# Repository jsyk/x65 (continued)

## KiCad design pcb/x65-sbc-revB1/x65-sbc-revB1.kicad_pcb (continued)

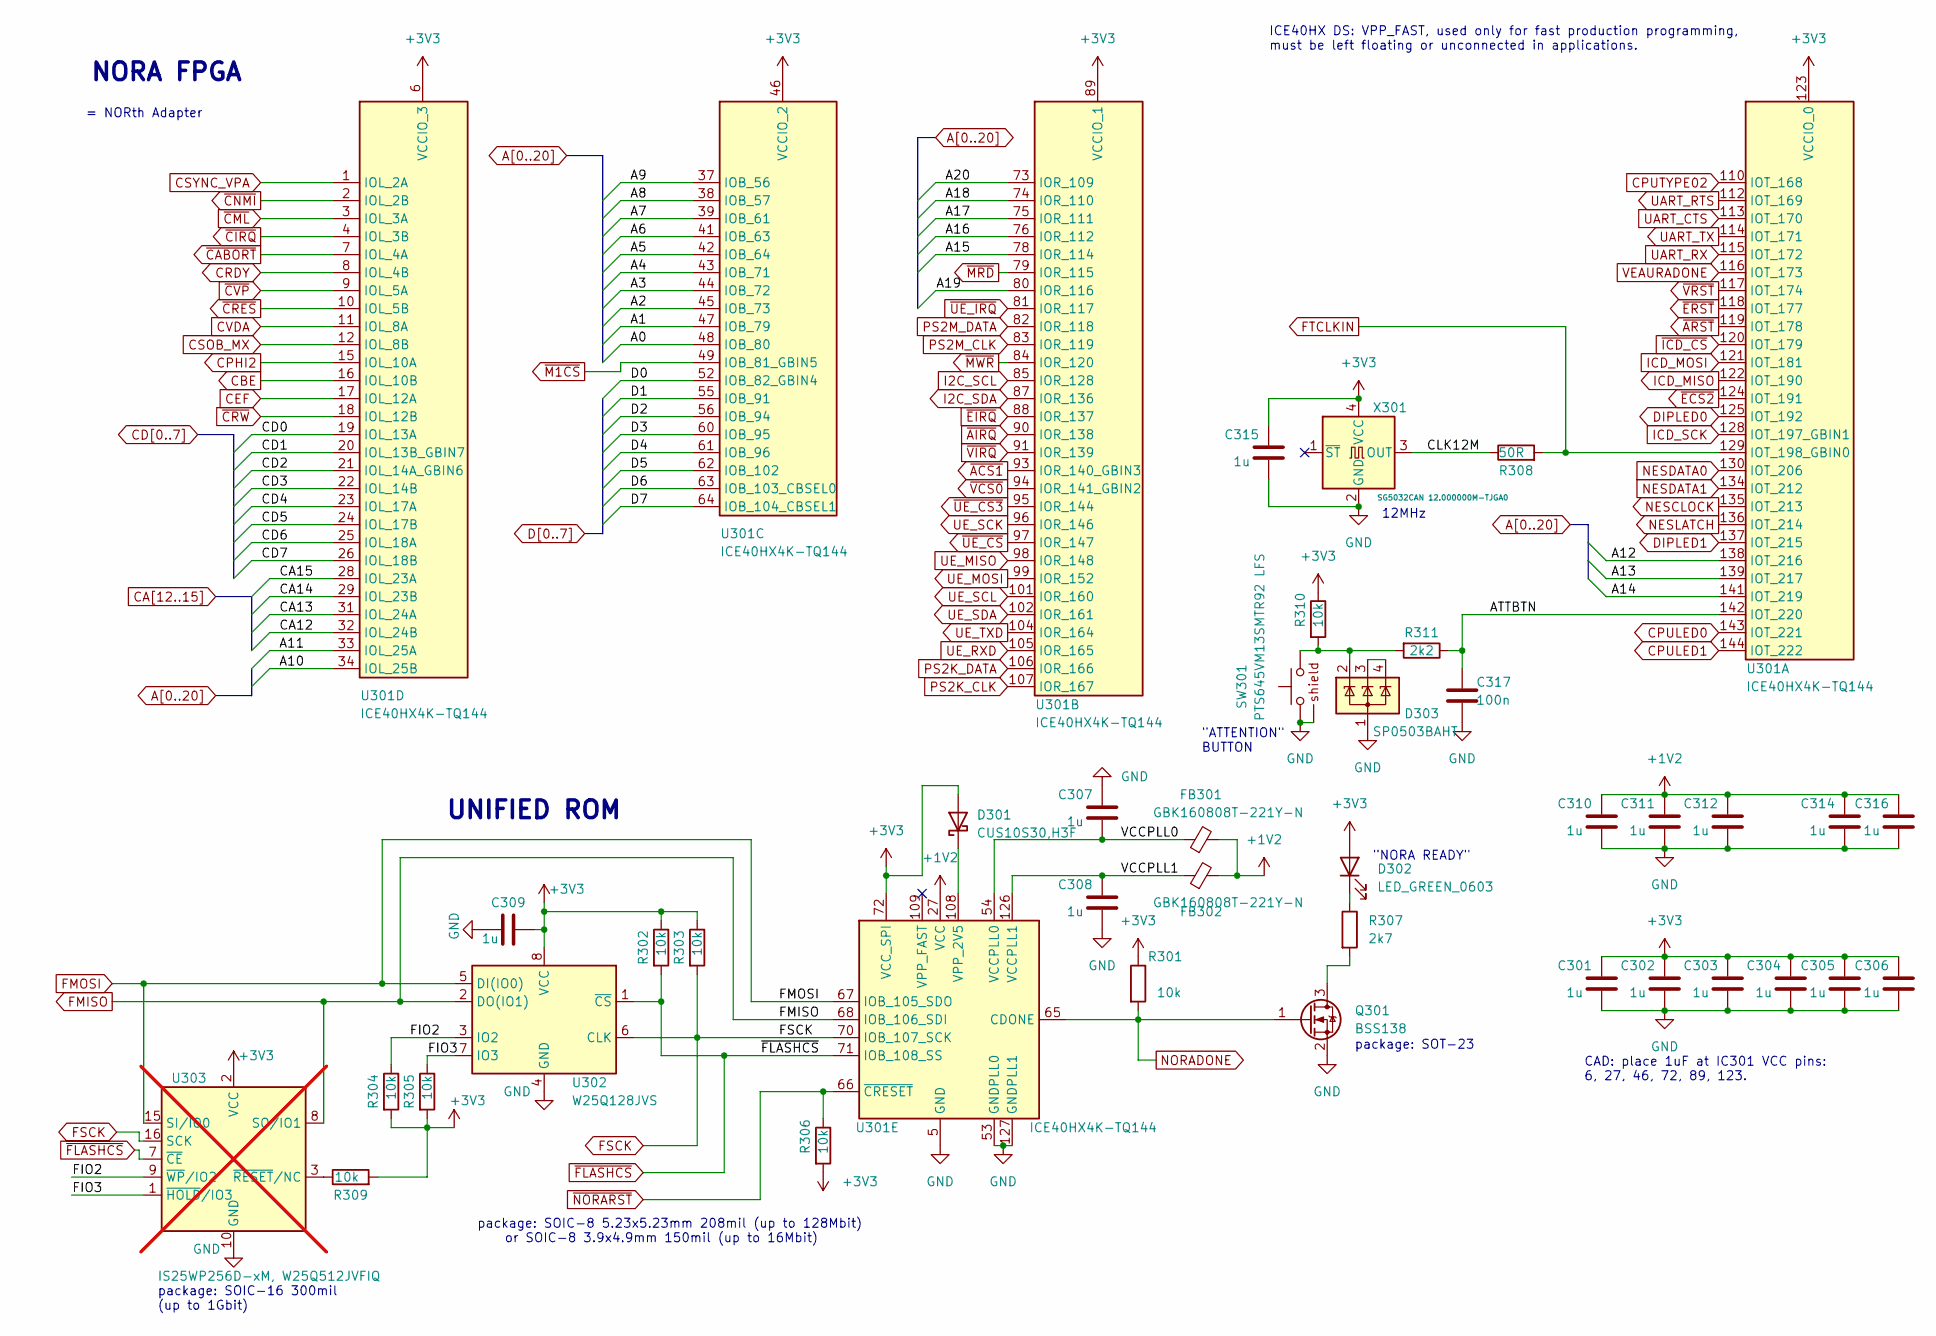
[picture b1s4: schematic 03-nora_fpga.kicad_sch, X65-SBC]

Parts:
C301, C302, C303, C304, C305, C306, C307, C308, C309, C310, C311, C312, C314, C315, C316: 1u; C_0603_1608Metric_Pad1.08x0.95mm_HandSolder
C317: 100n; C_0603_1608Metric_Pad1.08x0.95mm_HandSolder
D301: CUS10S30,H3F; D_SOD-323_HandSoldering
D302: LED_GREEN_0603; LED_0603_1608Metric_Pad1.05x0.95mm_HandSolder
D303: SP0503BAHT; SOT-143
FB301, FB302: GBK160808T-221Y-N; R_0603_1608Metric_Pad0.98x0.95mm_HandSolder
Q301: BSS138; SOT-23
R301, R302, R303, R304, R305, R306, R309, R310: 10k; R_0603_1608Metric_Pad0.98x0.95mm_HandSolder
R307: 2k7; R_0603_1608Metric_Pad0.98x0.95mm_HandSolder
R308: 50R; R_0603_1608Metric_Pad0.98x0.95mm_HandSolder
R311: 2k2; R_0603_1608Metric_Pad0.98x0.95mm_HandSolder
SW301: PTS645VM13SMTR92 LFS
U301: ICE40HX4K-TQ144; TQFP-144_20x20mm_P0.5mm
U302: W25Q128JVS; SOIC-8_5.23x5.23mm_P1.27mm_Extended
U303: IS25WP256D-xM, W25Q512JVFIQ; SOIC-16W_7.5x10.3mm_P1.27mm; not fitted
X301: SG5032CAN 12.000000M-TJGA0; Oscillator_SMD_SeikoEpson_SG8002LB-4Pin_5.0x3.2mm_HandSolde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

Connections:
+1V2: C310.1, C311.1, C312.1, C314.1, C316.1, FB301.2, FB302.2, U301.27 (VCC), U301.40 (VCC), U301.92 (VCC), U301.111 (VCC); also elsewhere on the board
+3V3: C301.1, C302.1, C303.1, C304.1, C305.1, C306.1, C309.1, C315.1, D301.2 (A), D302.2 (A), R301.1, R302.1, R303.1, R304.2, R305.2, R306.2, R309.2, R310.1, U301.6 (VCCIO_3), U301.30 (VCCIO_3), U301.46 (VCCIO_2), U301.57 (VCCIO_2), U301.72 (VCC_SPI), U301.89 (VCCIO_1), U301.100 (VCCIO_1), U301.123 (VCCIO_0), U301.131 (VCCIO_0), U302.8 (VCC), U303.2 (VCC), X301.4 (VCC); also elsewhere on the board
/NORA FPGA/ATTBTN: C317.1, R311.1, U301.142 (IOT_220)
/NORA FPGA/CLK12M: R308.1, X301.3 (OUT)
/NORA FPGA/FIO2: R304.1, U302.3 (IO2), U303.9 (~WP/IO2)
/NORA FPGA/FIO3: R305.1, U302.7 (IO3), U303.1 (~HOLD/IO3)
/NORA FPGA/VCCPLL0: C307.2, FB301.1, U301.54 (VCCPLL0)
/NORA FPGA/VCCPLL1: C308.1, FB302.1, U301.126 (VCCPLL1)
A0: U301.48 (IOB_80); also elsewhere on the board
A1: U301.47 (IOB_79); also elsewhere on the board
A2: U301.45 (IOB_73); also elsewhere on the board
A3: U301.44 (IOB_72); also elsewhere on the board
A4: U301.43 (IOB_71); also elsewhere on the board
A5: U301.42 (IOB_64); also elsewhere on the board
A6: U301.41 (IOB_63); also elsewhere on the board
A7: U301.39 (IOB_61); also elsewhere on the board
A8: U301.38 (IOB_57); also elsewhere on the board
A9: U301.37 (IOB_56); also elsewhere on the board
A10: U301.34 (IOL_25B); also elsewhere on the board
A11: U301.33 (IOL_25A); also elsewhere on the board
A12: U301.138 (IOT_216); also elsewhere on the board
A13: U301.139 (IOT_217); also elsewhere on the board
A14: U301.141 (IOT_219); also elsewhere on the board
A15: U301.78 (IOR_114); also elsewhere on the board
A16: U301.76 (IOR_112); also elsewhere on the board
A17: U301.75 (IOR_111); also elsewhere on the board
A18: U301.74 (IOR_110); also elsewhere on the board
A19: U301.80 (IOR_116); also elsewhere on the board
A20: U301.73 (IOR_109); also elsewhere on the board
CA12: U301.32 (IOL_24B); also elsewhere on the board
CA13: U301.31 (IOL_24A); also elsewhere on the board
CA14: U301.29 (IOL_23B); also elsewhere on the board
CA15: U301.28 (IOL_23A); also elsewhere on the board
CBE: U301.16 (IOL_10B); also elsewhere on the board
CD0: U301.19 (IOL_13A); also elsewhere on the board
CD1: U301.20 (IOL_13B_GBIN7); also elsewhere on the board
CD2: U301.21 (IOL_14A_GBIN6); also elsewhere on the board
CD3: U301.22 (IOL_14B); also elsewhere on the board
CD4: U301.23 (IOL_17A); also elsewhere on the board
CD5: U301.24 (IOL_17B); also elsewhere on the board
CD6: U301.25 (IOL_18A); also elsewhere on the board
CD7: U301.26 (IOL_18B); also elsewhere on the board
CEF: U301.17 (IOL_12A); also elsewhere on the board
CPHI2: U301.15 (IOL_10A); also elsewhere on the board
CPULED0: U301.143 (IOT_221); also elsewhere on the board
CPULED1: U301.144 (IOT_222); also elsewhere on the board
CPUTYPE02: U301.110 (IOT_168); also elsewhere on the board
CRDY: U301.8 (IOL_4B); also elsewhere on the board
CSOB_MX: U301.12 (IOL_8B); also elsewhere on the board
CSYNC_VPA: U301.1 (IOL_2A); also elsewhere on the board
CVDA: U301.11 (IOL_8A); also elsewhere on the board
D0: U301.52 (IOB_82_GBIN4); also elsewhere on the board
D1: U301.55 (IOB_91); also elsewhere on the board
D2: U301.56 (IOB_94); also elsewhere on the board
D3: U301.60 (IOB_95); also elsewhere on the board
D4: U301.61 (IOB_96); also elsewhere on the board
D5: U301.62 (IOB_102); also elsewhere on the board
D6: U301.63 (IOB_103_CBSEL0); also elsewhere on the board
D7: U301.64 (IOB_104_CBSEL1); also elsewhere on the board
DIPLED0: U301.125 (IOT_192); also elsewhere on the board
DIPLED1: U301.137 (IOT_215); also elsewhere on the board
FMISO: U301.68 (IOB_106_SDI), U302.2 (DO(IO1)), U303.8 (SO/IO1); also elsewhere on the board
FMOSI: U301.67 (IOB_105_SDO), U302.5 (DI(IO0)), U303.15 (SI/IO0); also elsewhere on the board
FSCK: R303.2, U301.70 (IOB_107_SCK), U302.6 (CLK), U303.16 (SCK); also elsewhere on the board
FTCLKIN: R308.2, U301.129 (IOT_198_GBIN0); also elsewhere on the board
GND: C301.2, C302.2, C303.2, C304.2, C305.2, C306.2, C307.1, C308.2, C309.2, C310.2, C311.2, C312.2, C314.2, C315.2, C316.2, C317.2, D303.1 (A), Q301.2 (S), SW301.1, SW301.SH, U301.5 (GND), U301.13 (GND), U301.14 (GND), U301.53 (GNDPLL0), U301.59 (GND), U301.69 (GND), U301.86 (GND), U301.103 (GND), U301.127 (GNDPLL1), U301.132 (GND), U301.140 (GND), U302.4 (GND), U303.10 (GND), X301.2 (GND); also elsewhere on the board
I2C_SCL: U301.85 (IOR_128); also elsewhere on the board
I2C_SDA: U301.87 (IOR_136); also elsewhere on the board
ICD_MISO: U301.122 (IOT_190); also elsewhere on the board
ICD_MOSI: U301.121 (IOT_181); also elsewhere on the board
ICD_SCK: U301.128 (IOT_197_GBIN1); also elsewhere on the board
NESCLOCK: U301.135 (IOT_213); also elsewhere on the board
NESDATA0: U301.130 (IOT_206); also elsewhere on the board
NESDATA1: U301.134 (IOT_212); also elsewhere on the board
NESLATCH: U301.136 (IOT_214); also elsewhere on the board
NORADONE: Q301.1 (G), R301.2, U301.65 (CDONE); also elsewhere on the board
unnamed: D301.1 (K), U301.108 (VPP_2V5)
unnamed: D302.1 (K), R307.1
unnamed: D303.2 (K), R310.2, R311.2, SW301.2
unnamed: D303.3 (K), D303.4 (K)
unnamed: Q301.3 (D), R307.2
unnamed: R309.1, U303.3 (~RESET/NC)
PS2K_CLK: U301.107 (IOR_167); also elsewhere on the board
PS2K_DATA: U301.106 (IOR_166); also elsewhere on the board
PS2M_CLK: U301.83 (IOR_119); also elsewhere on the board
PS2M_DATA: U301.82 (IOR_118); also elsewhere on the board
UART_CTS: U301.113 (IOT_170); also elsewhere on the board
UART_RTS: U301.112 (IOT_169); also elsewhere on the board
UART_RX: U301.115 (IOT_172); also elsewhere on the board
UART_TX: U301.114 (IOT_171); also elsewhere on the board
UE_MISO: U301.98 (IOR_148); also elsewhere on the board
UE_MOSI: U301.99 (IOR_152); also elsewhere on the board
UE_RXD: U301.105 (IOR_165); also elsewhere on the board
UE_SCK: U301.96 (IOR_146); also elsewhere on the board
UE_SCL: U301.101 (IOR_160); also elsewhere on the board
UE_SDA: U301.102 (IOR_161); also elsewhere on the board
UE_TXD: U301.104 (IOR_164); also elsewhere on the board
VEAURADONE: U301.116 (IOT_173); also elsewhere on the board
~ACS1: U301.93 (IOR_140_GBIN3); also elsewhere on the board
~AIRQ: U301.90 (IOR_138); also elsewhere on the board
~ARST: U301.119 (IOT_178); also elsewhere on the board
~CABORT: U301.7 (IOL_4A); also elsewhere on the board
~CIRQ: U301.4 (IOL_3B); also elsewhere on the board
~CML: U301.3 (IOL_3A); also elsewhere on the board
~CNMI: U301.2 (IOL_2B); also elsewhere on the board
~CRES: U301.10 (IOL_5B); also elsewhere on the board
~CRW: U301.18 (IOL_12B); also elsewhere on the board
~CVP: U301.9 (IOL_5A); also elsewhere on the board
~ECS2: U301.124 (IOT_191); also elsewhere on the board
~EIRQ: U301.88 (IOR_137); also elsewhere on the board
~ERST: U301.118 (IOT_177); also elsewhere on the board
~FLASHCS: R302.2, U301.71 (IOB_108_SS), U302.1 (~CS), U303.7 (~CE); also elsewhere on the board
~ICD_CS: U301.120 (IOT_179); also elsewhere on the board
~M1CS: U301.49 (IOB_81_GBIN5); also elsewhere on the board
~MRD: U301.79 (IOR_115); also elsewhere on the board
~MWR: U301.84 (IOR_120); also elsewhere on the board
~NORARST: R306.1, U301.66 (~CRESET); also elsewhere on the board
~UE_CS3: U301.95 (IOR_144); also elsewhere on the board
~UE_CS: U301.97 (IOR_147); also elsewhere on the board
~UE_IRQ: U301.81 (IOR_117); also elsewhere on the board
~VCS0: U301.94 (IOR_141_GBIN2); also elsewhere on the board
~VIRQ: U301.91 (IOR_139); also elsewhere on the board
~VRST: U301.117 (IOT_174); also elsewhere on the board

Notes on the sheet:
package: SOIC-8 5.23x5.23mm 208mil (up to 128Mbit) or SOIC-8 3.9x4.9mm 150mil (up to 16Mbit)
12MHz
= NORth Adapter
ICE40HX DS: VPP_FAST, used only for fast production programming, must be left floating or unconnected in applications.
"NORA READY"
NORA FPGA
UNIFIED ROM
package: SOIC-16 300mil (up to 1Gbit)
package: SOT-23
"ATTENTION" BUTTON
CAD: place 1uF at IC301 VCC pins: 6, 27, 46, 72, 89, 123.

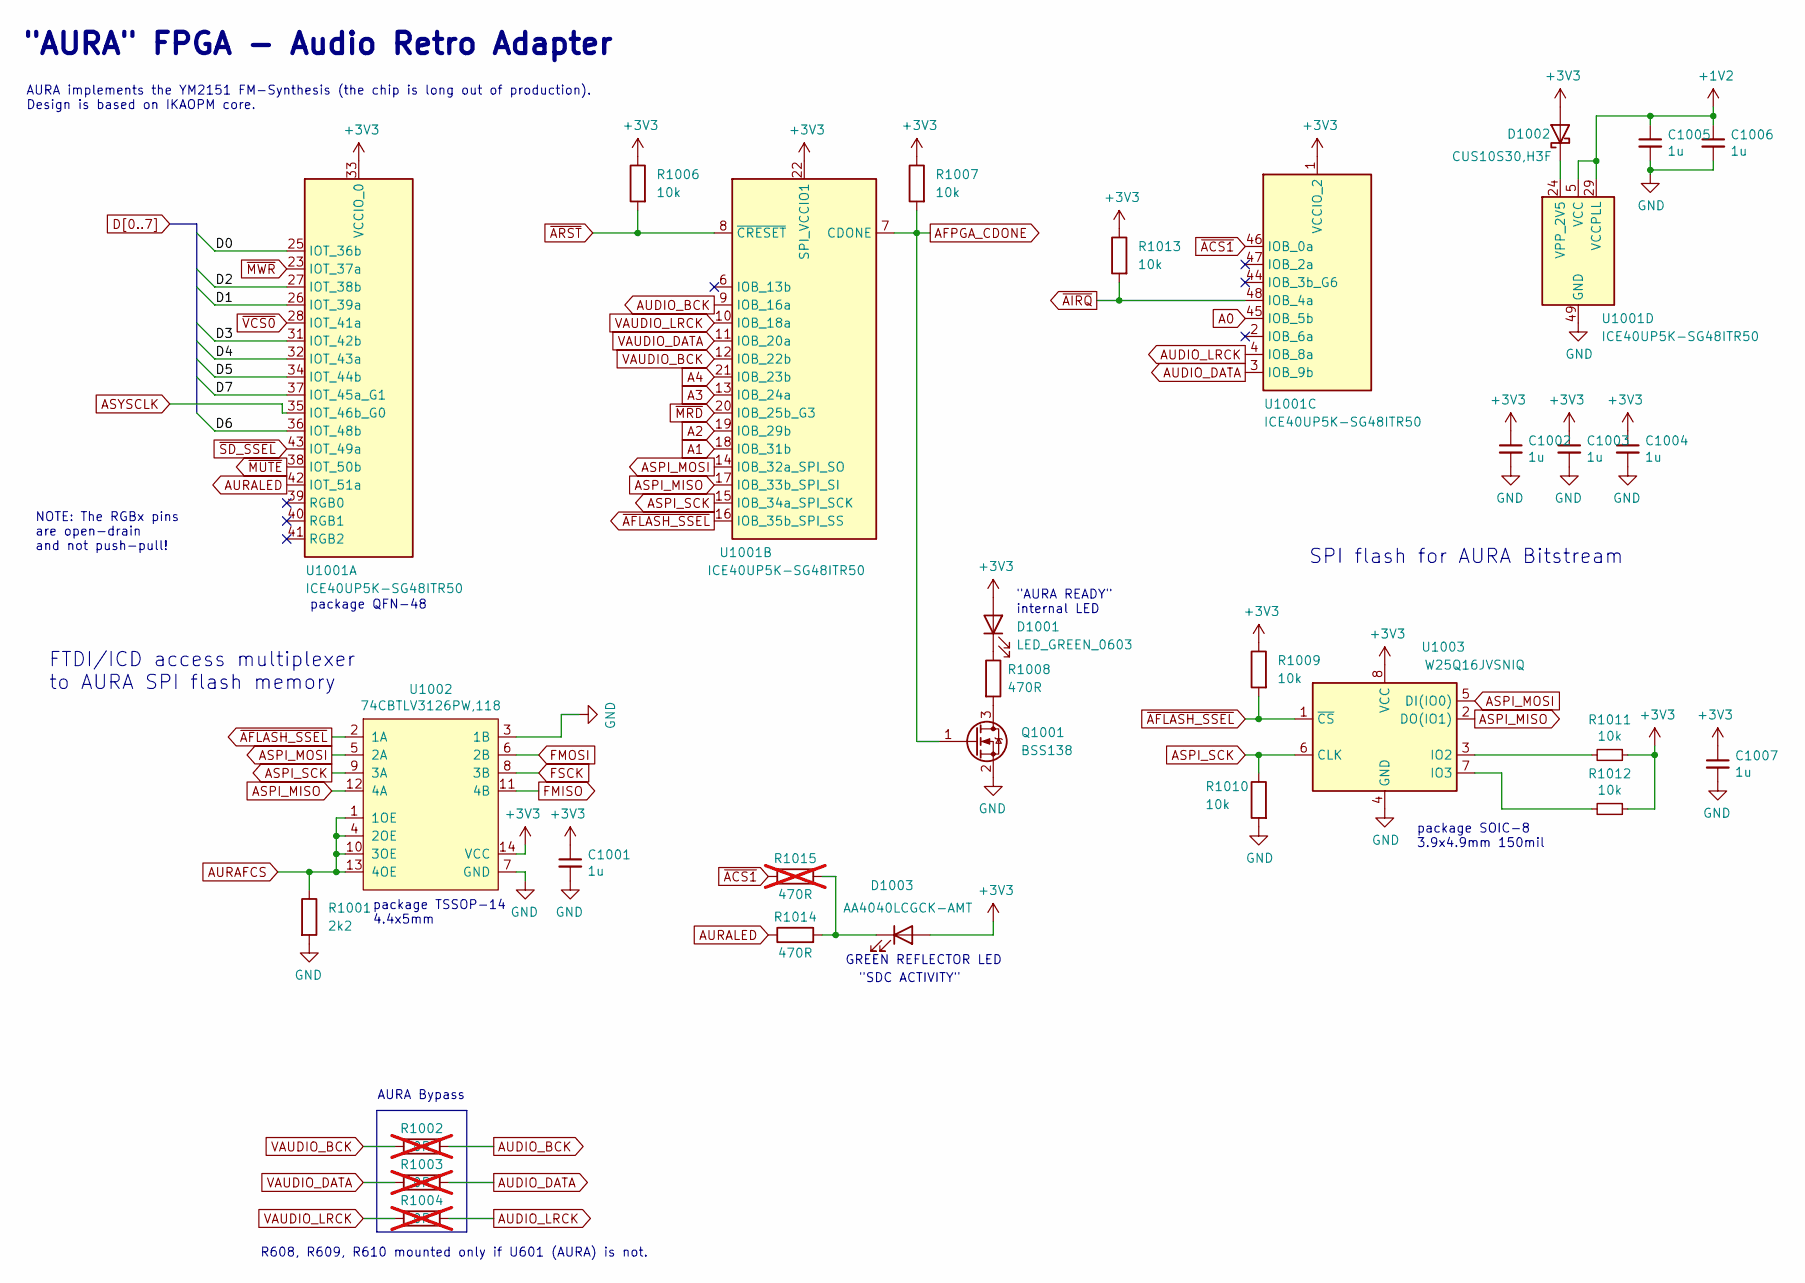
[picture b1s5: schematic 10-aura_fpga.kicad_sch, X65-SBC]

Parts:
C1001, C1002, C1003, C1004, C1005, C1006, C1007: 1u; C_0603_1608Metric_Pad1.08x0.95mm_HandSolder
D1001: LED_GREEN_0603; LED_0603_1608Metric_Pad1.05x0.95mm_HandSolder
D1002: CUS10S30,H3F; D_SOD-323_HandSoldering
D1003: AA4040LCGCK-AMT; PLCC2_4x4mm
Q1001: BSS138; SOT-23
R1001: 2k2; R_0603_1608Metric_Pad0.98x0.95mm_HandSolder
R1002, R1003, R1004: 0R; R_0603_1608Metric_Pad0.98x0.95mm_HandSolder; not fitted
R1006, R1007, R1009, R1010, R1011, R1012, R1013: 10k; R_0603_1608Metric_Pad0.98x0.95mm_HandSolder
R1008, R1014: 470R; R_0603_1608Metric_Pad0.98x0.95mm_HandSolder
R1015: 470R; R_0603_1608Metric_Pad0.98x0.95mm_HandSolder; not fitted
U1001: ICE40UP5K-SG48ITR50; QFN-48-1EP_7x7mm_P0.5mm_EP5.3x5.3mm
U1002: 74CBTLV3126PW,118; TSSOP-14_4.4x5mm_P0.65mm
U1003: W25Q16JVSNIQ; SOIC-8_3.9x4.9mm_P1.27mm

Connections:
+1V2: C1005.1, C1006.1, U1001.5 (VCC), U1001.29 (VCCPLL), U1001.30 (VCC); also elsewhere on the board
+3V3: C1001.1, C1002.1, C1003.1, C1004.1, C1007.1, D1001.2 (A), D1002.2 (A), D1003.2 (A), R1006.1, R1007.1, R1009.1, R1011.1, R1012.1, R1013.1, U1001.1 (VCCIO_2), U1001.22 (SPI_VCCIO1), U1001.33 (VCCIO_0), U1002.14 (VCC), U1003.8 (VCC); also elsewhere on the board
A0: U1001.45 (IOB_5b); also elsewhere on the board
A1: U1001.18 (IOB_31b); also elsewhere on the board
A2: U1001.19 (IOB_29b); also elsewhere on the board
A3: U1001.13 (IOB_24a); also elsewhere on the board
A4: U1001.21 (IOB_23b); also elsewhere on the board
AFPGA_CDONE: Q1001.1 (G), R1007.2, U1001.7 (CDONE); also elsewhere on the board
ASPI_MISO: U1001.17 (IOB_33b_SPI_SI), U1002.12 (4A), U1003.2 (DO(IO1))
ASPI_MOSI: U1001.14 (IOB_32a_SPI_SO), U1002.5 (2A), U1003.5 (DI(IO0))
ASPI_SCK: R1010.1, U1001.15 (IOB_34a_SPI_SCK), U1002.9 (3A), U1003.6 (CLK)
ASYSCLK: U1001.35 (IOT_46b_G0); also elsewhere on the board
AUDIO_BCK: R1002.2, U1001.9 (IOB_16a); also elsewhere on the board
AUDIO_DATA: R1003.2, U1001.3 (IOB_9b); also elsewhere on the board
AUDIO_LRCK: R1004.2, U1001.4 (IOB_8a); also elsewhere on the board
AURAFCS: R1001.1, U1002.1 (1OE), U1002.4 (2OE), U1002.10 (3OE), U1002.13 (4OE); also elsewhere on the board
AURALED: R1014.1, U1001.42 (IOT_51a)
D0: U1001.25 (IOT_36b); also elsewhere on the board
D1: U1001.26 (IOT_39a); also elsewhere on the board
D2: U1001.27 (IOT_38b); also elsewhere on the board
D3: U1001.31 (IOT_42b); also elsewhere on the board
D4: U1001.32 (IOT_43a); also elsewhere on the board
D5: U1001.34 (IOT_44b); also elsewhere on the board
D6: U1001.36 (IOT_48b); also elsewhere on the board
D7: U1001.37 (IOT_45a_G1); also elsewhere on the board
FMISO: U1002.11 (4B); also elsewhere on the board
FMOSI: U1002.6 (2B); also elsewhere on the board
FSCK: U1002.8 (3B); also elsewhere on the board
GND: C1001.2, C1002.2, C1003.2, C1004.2, C1005.2, C1006.2, C1007.2, Q1001.2 (S), R1001.2, R1010.2, U1001.49 (GND), U1002.3 (1B), U1002.7 (GND), U1003.4 (GND); also elsewhere on the board
unnamed: D1001.1 (K), R1008.1
unnamed: D1002.1 (K), U1001.24 (VPP_2V5)
unnamed: D1003.1 (K), R1014.2, R1015.2
unnamed: Q1001.3 (D), R1008.2
unnamed: R1011.2, U1003.3 (IO2)
unnamed: R1012.2, U1003.7 (IO3)
VAUDIO_BCK: R1002.1, U1001.12 (IOB_22b); also elsewhere on the board
VAUDIO_DATA: R1003.1, U1001.11 (IOB_20a); also elsewhere on the board
VAUDIO_LRCK: R1004.1, U1001.10 (IOB_18a); also elsewhere on the board
~ACS1: R1015.1, U1001.46 (IOB_0a); also elsewhere on the board
~AFLASH_SSEL: R1009.2, U1001.16 (IOB_35b_SPI_SS), U1002.2 (1A), U1003.1 (~CS)
~AIRQ: R1013.2, U1001.48 (IOB_4a); also elsewhere on the board
~ARST: R1006.2, U1001.8 (~CRESET); also elsewhere on the board
~MRD: U1001.20 (IOB_25b_G3); also elsewhere on the board
~MUTE: U1001.38 (IOT_50b); also elsewhere on the board
~MWR: U1001.23 (IOT_37a); also elsewhere on the board
~SD_SSEL: U1001.43 (IOT_49a); also elsewhere on the board
~VCS0: U1001.28 (IOT_41a); also elsewhere on the board

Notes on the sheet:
R608, R609, R610 mounted only if U601 (AURA) is not.
package TSSOP-14 4.4x5mm
"AURA" FPGA - Audio Retro Adapter
GREEN REFLECTOR LED
FTDI/ICD access multiplexer to AURA SPI flash memory
SPI flash for AURA Bitstream
package QFN-48
"SDC ACTIVITY"
AURA Bypass
NOTE: The RGBx pins are open-drain and not push-pull!
package SOIC-8 3.9x4.9mm 150mil
"AURA READY" internal LED
AURA implements the YM2151 FM-Synthesis (the chip is long out of production). Design is based on IKAOPM core.

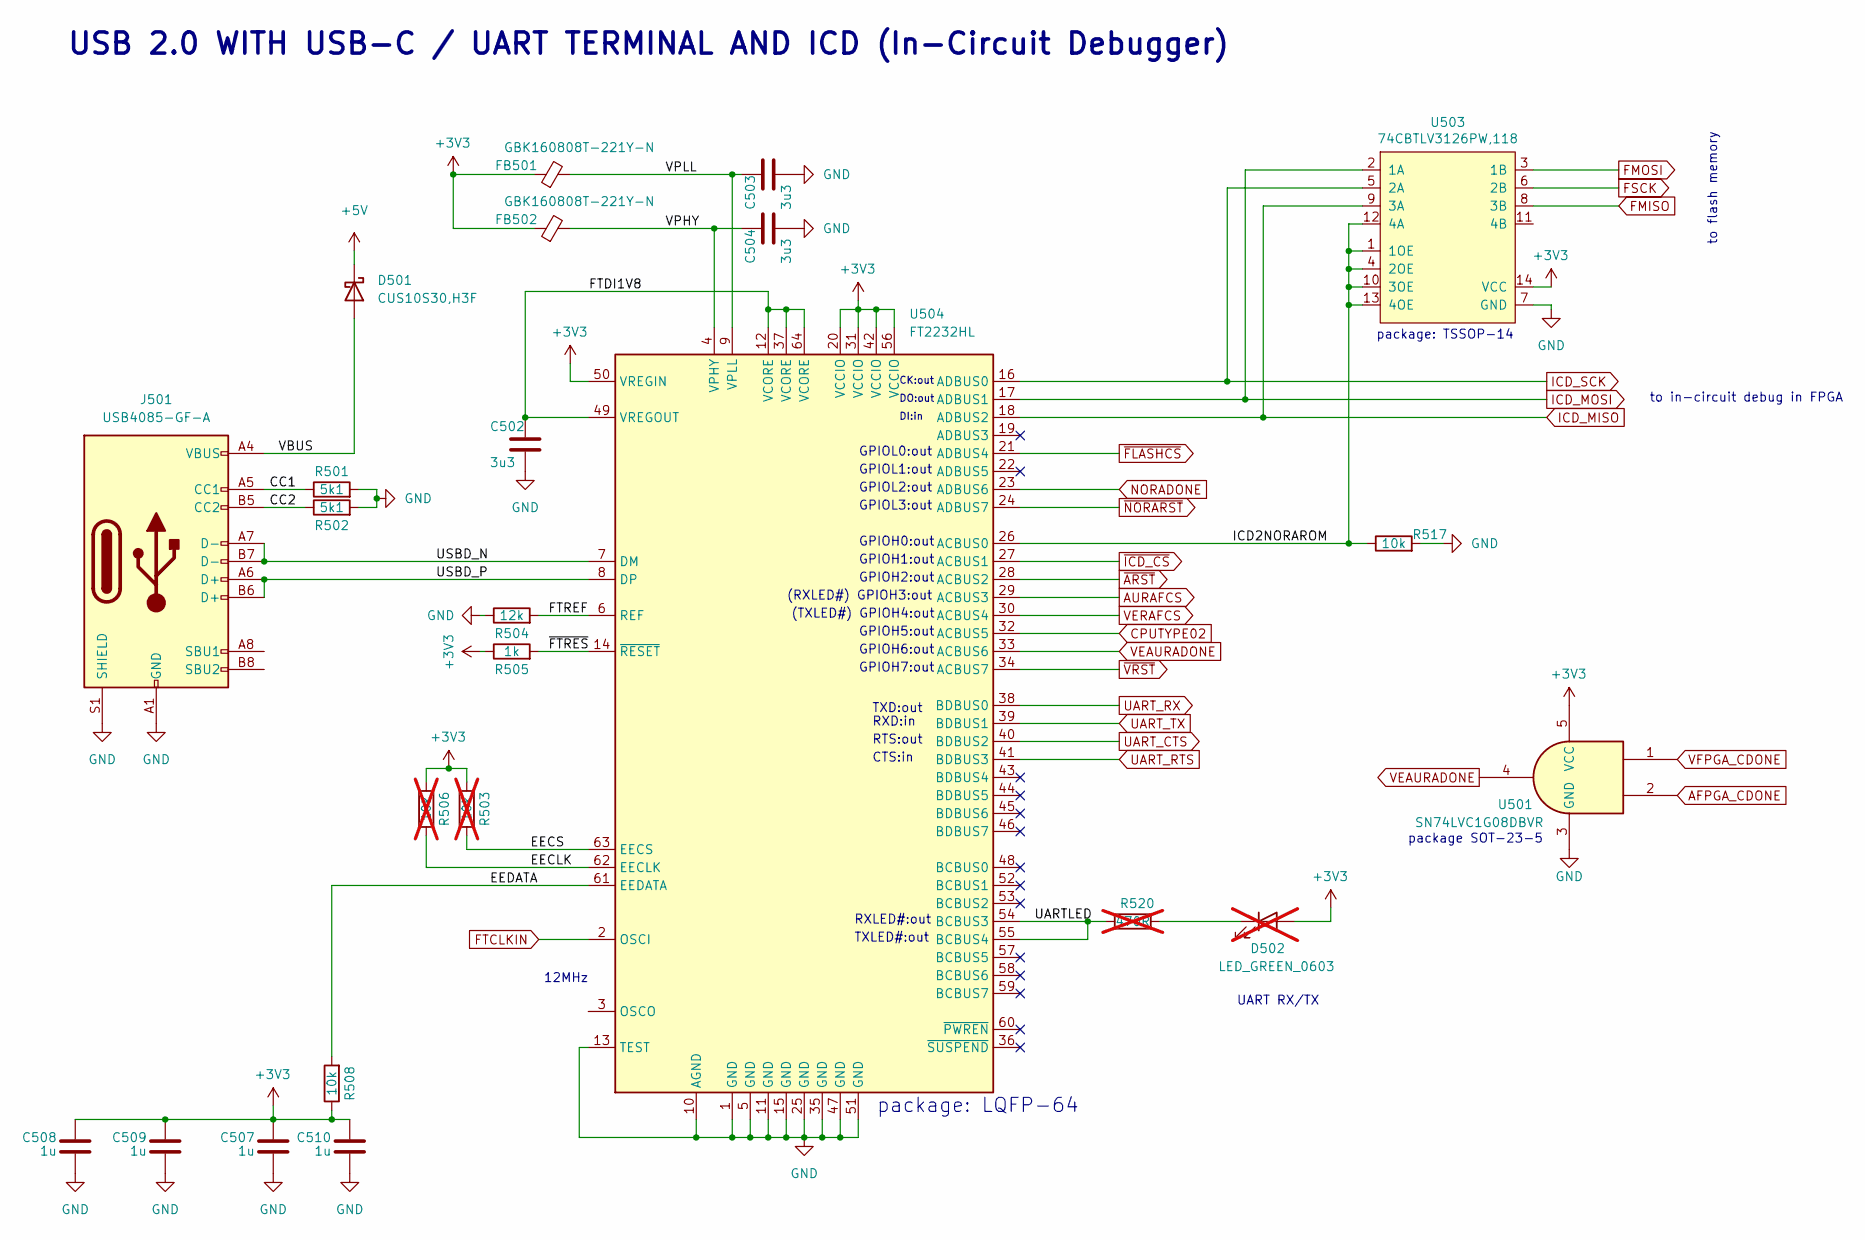
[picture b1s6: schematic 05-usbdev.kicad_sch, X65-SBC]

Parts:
C502, C503, C504: 3u3; C_0603_1608Metric_Pad1.08x0.95mm_HandSolder
C507, C508, C509, C510: 1u; C_0603_1608Metric_Pad1.08x0.95mm_HandSolder
D501: CUS10S30,H3F; D_SOD-323_HandSoldering
D502: LED_GREEN_0603; LED_0603_1608Metric_Pad1.05x0.95mm_HandSolder; not fitted
FB501, FB502: GBK160808T-221Y-N; R_0603_1608Metric_Pad0.98x0.95mm_HandSolder
J501: USB4085-GF-A; USB_C_Receptacle_GCT_USB4085
R501, R502: 5k1; R_0603_1608Metric_Pad0.98x0.95mm_HandSolder
R503, R506: 10k; R_0603_1608Metric_Pad0.98x0.95mm_HandSolder; not fitted
R504: 12k; R_0603_1608Metric_Pad0.98x0.95mm_HandSolder
R505: 1k; R_0603_1608Metric_Pad0.98x0.95mm_HandSolder
R508, R517: 10k; R_0603_1608Metric_Pad0.98x0.95mm_HandSolder
R520: 470R; R_0603_1608Metric_Pad0.98x0.95mm_HandSolder; not fitted
U501: SN74LVC1G08DBVR; SOT-23-5_HandSoldering
U503: 74CBTLV3126PW,118; TSSOP-14_4.4x5mm_P0.65mm
U504: FT2232HL; LQFP-64_10x10mm_P0.5mm

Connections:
+3V3: C507.1, C508.1, C509.1, C510.1, D502.2 (A), FB501.1, FB502.1, R503.2, R505.1, R506.2, R508.1, U501.5 (VCC), U503.14 (VCC), U504.20 (VCCIO), U504.31 (VCCIO), U504.42 (VCCIO), U504.50 (VREGIN), U504.56 (VCCIO); also elsewhere on the board
+5V: D501.1 (K); also elsewhere on the board
/USB-Terminal/CC1: J501.A5 (CC1), R501.1
/USB-Terminal/CC2: J501.B5 (CC2), R502.1
/USB-Terminal/EECLK: R506.1, U504.62 (EECLK)
/USB-Terminal/EECS: R503.1, U504.63 (EECS)
/USB-Terminal/EEDATA: R508.2, U504.61 (EEDATA)
/USB-Terminal/FTDI1V8: C502.1, U504.12 (VCORE), U504.37 (VCORE), U504.49 (VREGOUT), U504.64 (VCORE)
/USB-Terminal/FTREF: R504.2, U504.6 (REF)
/USB-Terminal/ICD2NORAROM: R517.1, U503.1 (1OE), U503.4 (2OE), U503.10 (3OE), U503.12 (4A), U503.13 (4OE), U504.26 (ACBUS0)
/USB-Terminal/UARTLED: R520.1, U504.54 (BCBUS3), U504.55 (BCBUS4)
/USB-Terminal/USBD_N: J501.A7 (D-), J501.B7 (D-), U504.7 (DM)
/USB-Terminal/USBD_P: J501.A6 (D+), J501.B6 (D+), U504.8 (DP)
/USB-Terminal/VBUS: D501.2 (A), J501.A4 (VBUS), J501.A9 (VBUS), J501.B4 (VBUS), J501.B9 (VBUS)
/USB-Terminal/VPHY: C504.1, FB502.2, U504.4 (VPHY)
/USB-Terminal/VPLL: C503.1, FB501.2, U504.9 (VPLL)
/USB-Terminal/~FTRES: R505.2, U504.14 (~RESET)
AFPGA_CDONE: U501.2; also elsewhere on the board
AURAFCS: U504.29 (ACBUS3); also elsewhere on the board
CPUTYPE02: U504.32 (ACBUS5); also elsewhere on the board
FMISO: U503.8 (3B); also elsewhere on the board
FMOSI: U503.3 (1B); also elsewhere on the board
FSCK: U503.6 (2B); also elsewhere on the board
FTCLKIN: U504.2 (OSCI); also elsewhere on the board
GND: C502.2, C503.2, C504.2, C507.2, C508.2, C509.2, C510.2, J501.A1 (GND), J501.A12 (GND), J501.B1 (GND), J501.B12 (GND), J501.S1 (SHIELD), R501.2, R502.2, R504.1, R517.2, U501.3 (GND), U503.7 (GND), U504.1 (GND), U504.5 (GND), U504.10 (AGND), U504.11 (GND), U504.13 (TEST), U504.15 (GND), U504.25 (GND), U504.35 (GND), U504.47 (GND), U504.51 (GND); also elsewhere on the board
ICD_MISO: U503.9 (3A), U504.18 (ADBUS2); also elsewhere on the board
ICD_MOSI: U503.2 (1A), U504.17 (ADBUS1); also elsewhere on the board
ICD_SCK: U503.5 (2A), U504.16 (ADBUS0); also elsewhere on the board
NORADONE: U504.23 (ADBUS6); also elsewhere on the board
unnamed: D502.1 (K), R520.2
UART_CTS: U504.40 (BDBUS2); also elsewhere on the board
UART_RTS: U504.41 (BDBUS3); also elsewhere on the board
UART_RX: U504.38 (BDBUS0); also elsewhere on the board
UART_TX: U504.39 (BDBUS1); also elsewhere on the board
VEAURADONE: U501.4, U504.33 (ACBUS6); also elsewhere on the board
VERAFCS: U504.30 (ACBUS4); also elsewhere on the board
VFPGA_CDONE: U501.1; also elsewhere on the board
~ARST: U504.28 (ACBUS2); also elsewhere on the board
~FLASHCS: U504.21 (ADBUS4); also elsewhere on the board
~ICD_CS: U504.27 (ACBUS1); also elsewhere on the board
~NORARST: U504.24 (ADBUS7); also elsewhere on the board
~VRST: U504.34 (ACBUS7); also elsewhere on the board

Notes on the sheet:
GPIOH6:out
GPIOL0:out
12MHz
TXLED#:out
CK:out
to in-circuit debug in FPGA
RXLED#:out
(RXLED#) GPIOH3:out
GPIOL3:out
(TXLED#) GPIOH4:out
GPIOH1:out
RTS:out
GPIOH2:out
package: LQFP-64
to flash memory
GPIOL2:out
CTS:in
DI:in
package: TSSOP-14
GPIOL1:out
DO:out
UART RX/TX
RXD:in
GPIOH7:out
TXD:out
package SOT-23-5
GPIOH5:out
USB 2.0 WITH USB-C / UART TERMINAL AND ICD (In-Circuit Debugger)
GPIOH0:out

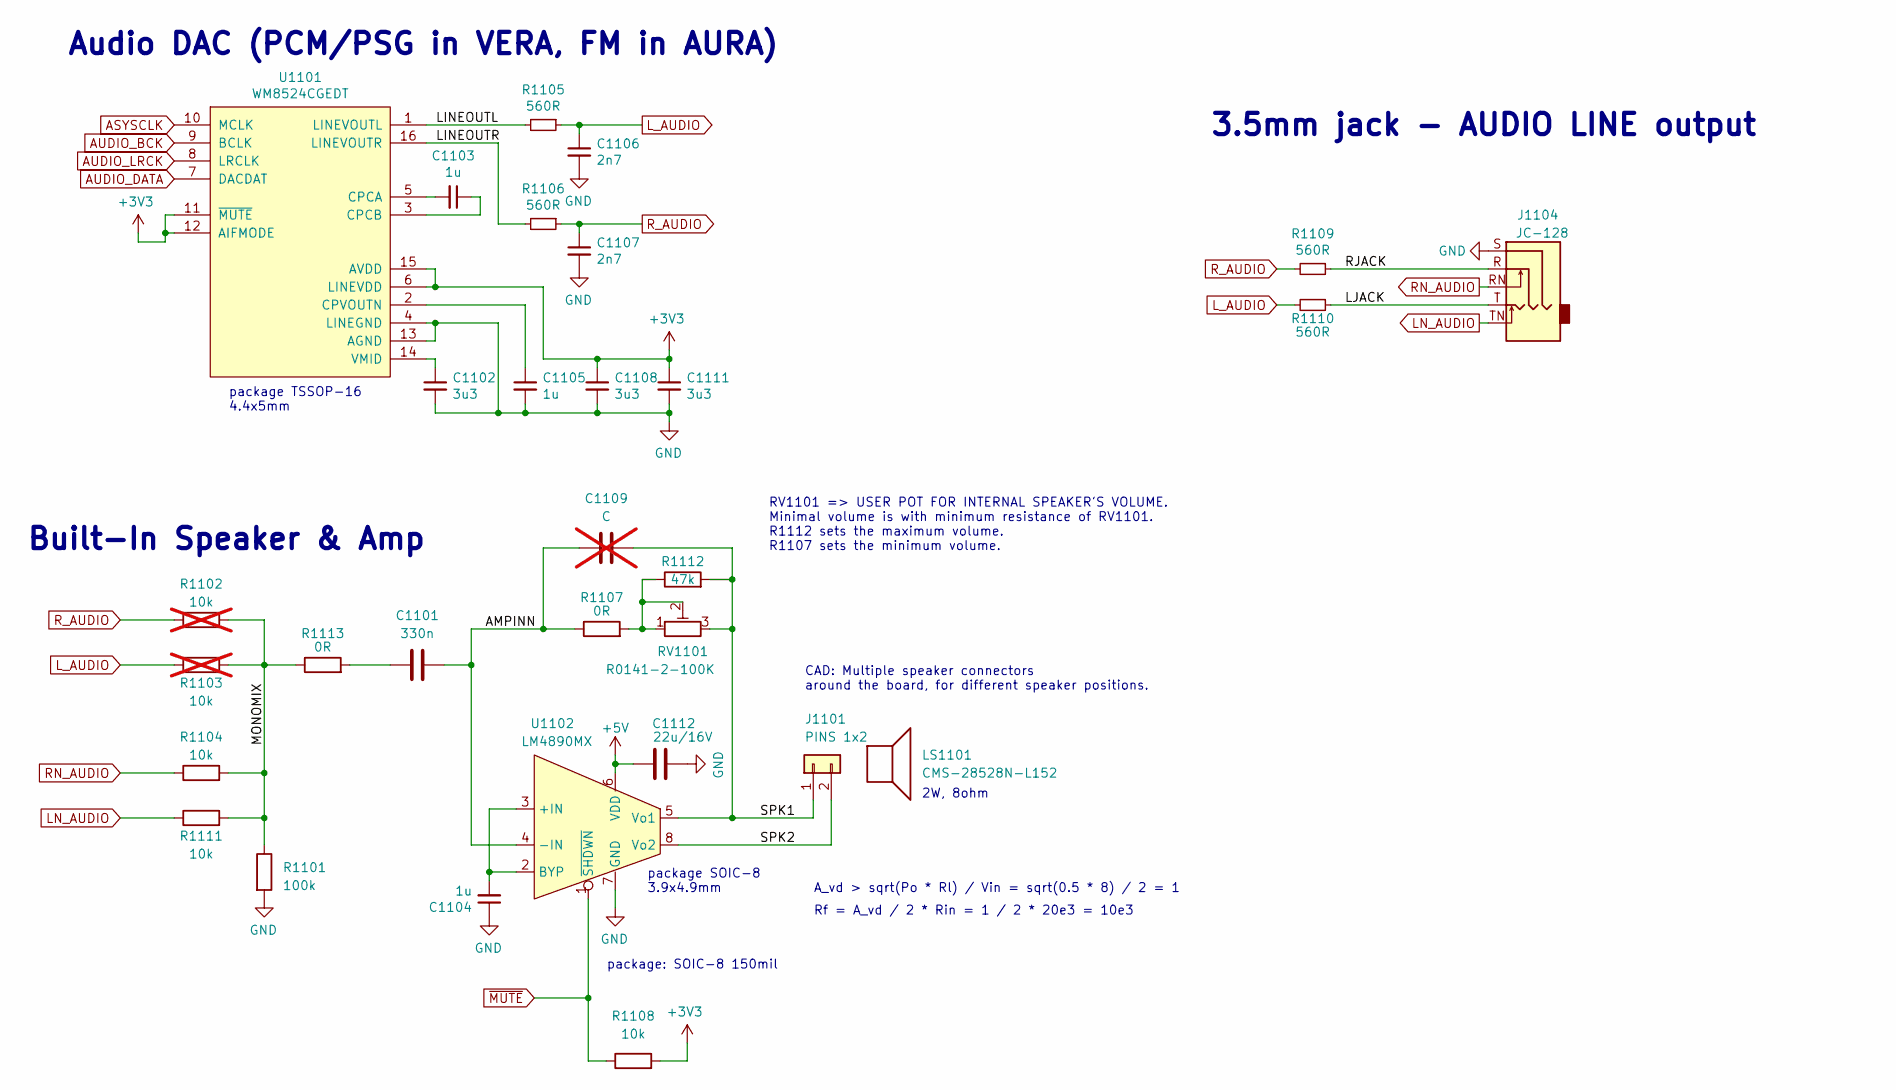
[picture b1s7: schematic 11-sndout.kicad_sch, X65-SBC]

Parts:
C1101: 330n; C_0603_1608Metric_Pad1.08x0.95mm_HandSolder
C1102, C1108, C1111: 3u3; C_0603_1608Metric_Pad1.08x0.95mm_HandSolder
C1103, C1104, C1105: 1u; C_0603_1608Metric_Pad1.08x0.95mm_HandSolder
C1106, C1107: 2n7; C_0603_1608Metric_Pad1.08x0.95mm_HandSolder
C1109: C; C_0603_1608Metric_Pad1.08x0.95mm_HandSolder; not fitted
C1112: 22u/16V; C_0805_2012Metric_Pad1.18x1.45mm_HandSolder
J1101: PINS 1x2; PinHeader_1x02_P2.54mm_Horizontal
J1104: JC-128
LS1101: CMS-28528N-L152
R1101: 100k; R_0603_1608Metric_Pad0.98x0.95mm_HandSolder
R1102, R1103: 10k; R_0603_1608Metric_Pad0.98x0.95mm_HandSolder; not fitted
R1104, R1108, R1111: 10k; R_0603_1608Metric_Pad0.98x0.95mm_HandSolder
R1105, R1106, R1109, R1110: 560R; R_0603_1608Metric_Pad0.98x0.95mm_HandSolder
R1107, R1113: 0R; R_0603_1608Metric_Pad0.98x0.95mm_HandSolder
R1112: 47k; R_0603_1608Metric_Pad0.98x0.95mm_HandSolder
RV1101: R0141-2-100K; Trimmer_R0141-2
U1101: WM8524CGEDT; TSSOP-16_4.4x5mm_P0.65mm
U1102: LM4890MX; SOIC-8_3.9x4.9mm_P1.27mm

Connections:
+3V3: C1108.1, C1111.1, R1108.2, U1101.6 (LINEVDD), U1101.11 (~MUTE), U1101.12 (AIFMODE), U1101.15 (AVDD); also elsewhere on the board
+5V: C1112.2, U1102.6 (VDD); also elsewhere on the board
/Sound Output/AMPINN: C1101.2, C1109.1, R1107.1, U1102.4 (-IN)
/Sound Output/LINEOUTL: R1105.2, U1101.1 (LINEVOUTL)
/Sound Output/LINEOUTR: R1106.2, U1101.16 (LINEVOUTR)
/Sound Output/LJACK: J1104.T, R1110.1
/Sound Output/MONOMIX: R1101.1, R1102.2, R1103.2, R1104.2, R1111.2, R1113.1
/Sound Output/RJACK: J1104.R, R1109.1
/Sound Output/SPK1: C1109.2, J1101.1, R1112.2, RV1101.3, U1102.5 (Vo1)
/Sound Output/SPK2: J1101.2, U1102.8 (Vo2)
ASYSCLK: U1101.10 (MCLK); also elsewhere on the board
AUDIO_BCK: U1101.9 (BCLK); also elsewhere on the board
AUDIO_DATA: U1101.7 (DACDAT); also elsewhere on the board
AUDIO_LRCK: U1101.8 (LRCLK); also elsewhere on the board
GND: C1102.2, C1104.1, C1105.2, C1106.2, C1107.2, C1108.2, C1111.2, C1112.1, J1104.S, R1101.2, U1101.4 (LINEGND), U1101.13 (AGND), U1102.7 (GND); also elsewhere on the board
LN_AUDIO: J1104.TN, R1111.1
L_AUDIO: C1106.1, R1103.1, R1105.1, R1110.2
unnamed: C1101.1, R1113.2
unnamed: R1107.2, R1112.1, RV1101.1, RV1101.2
unnamed: C1103.2, U1101.5 (CPCA)
unnamed: C1103.1, U1101.3 (CPCB)
unnamed: C1105.1, U1101.2 (CPVOUTN)
unnamed: C1102.1, U1101.14 (VMID)
unnamed: C1104.2, U1102.2 (BYP), U1102.3 (+IN)
RN_AUDIO: J1104.RN, R1104.1
R_AUDIO: C1107.1, R1102.1, R1106.1, R1109.2
~MUTE: R1108.1, U1102.1 (~SHDWN); also elsewhere on the board

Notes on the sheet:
Built-In Speaker & Amp
package TSSOP-16 4.4x5mm
3.5mm jack - AUDIO LINE output
CAD: Multiple speaker connectors around the board, for different speaker positions.
2W, 8ohm
A_vd > sqrt(Po * Rl) / Vin = sqrt(0.5 * 8) / 2 = 1
RV1101 => USER POT FOR INTERNAL SPEAKER'S VOLUME. Minimal volume is with minimum resistance of RV1101. R1112 sets the maximum volume. R1107 sets the minimum volume.
package: SOIC-8 150mil
Audio DAC (PCM/PSG in VERA, FM in AURA)
package SOIC-8 3.9x4.9mm
Rf = A_vd / 2 * Rin = 1 / 2 * 20e3 = 10e3
